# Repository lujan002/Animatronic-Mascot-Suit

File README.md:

# Junior-Jay Animatronic Mascot 

Watch overview video [here](https://youtu.be/p1z4z74mzpA)

The scope of this project was to develop a wearable, Disney-style, animatronic suit with actuated facial features for the University of Kansas's flagship line of "Jayhawk" mascots. The project was sponsored by the Mechanical Engineering Department at the University of Kansas, with the primary client being the University of Kansas head mascot coach. The initiative aimed to revolutionize the university's mascot program by incorporating advanced, expressive features into a new mascot called "Junior Jay". The primary requirements outlined by the client included the ability for the mascots to display a wide range of dynamic, real-time facial expressions, like those seen in professionally animated characters. 

Designing an entirely new mascot head from the ground up was not feasible for the financial and time contraints of this project, so the University of Kansas athletics department graciously donated a retired "Baby Jay" mascot head for the team to retrofit into a proof-of-concept prototype for Junior Jay. Without their support, this project would not be possible. 

This project provided a great mix of mechanical, electrical, and software engineering challanges. The engineering objectives were to modify this retired mascot head with seamless control of the mouth, eyebrow, and eyelid actuation mechanisms using custom facial expression detection & control software, while maintaining durability, comfort, and ease of use. The project started in Aug. 2023 with initial drafts of mechanical models, code, and electrical schematics, then concluded in late Apr. 2024 with a functional protoype that met the majority of our project objectives. Below will be an outline of the final state of these three systems. 

## Mechanism Sub-Systems
### Beak  

Goal: Open/close beak to simulate smile, shock.

The beak assembly consisted of a lightweight aluminum frame inserted into the original, detached foam beak to provide rigidity and a means for the servo motors to drive the beak. We selected servos rated for 45 kg·cm of torque, suitable for the high-torque demands of our application. This choice was driven by the requirement to counter the beak weight of 0.7 kg (6.87 N), with center of gravity centered 230 mm away (1.58 Nm Torque). After installation, the foam beak was re-stitched to the rest of the head for aesthetic purposes. A primary focus was on ensuring robustness and minimizing weight, and the final frame design shown below was no more than 0.4 kg. 

### Eyebrows  

Goal: Rotate eyebrows to display nuanced emotions. 

To enable the mascot to express nuanced emotions, precise control over the eyebrows was essential. The final design acheived this by incorporating each eyebrow as one of the links in a three-bar linkage driven by two servos. This gave each eyebrow two ways to pivot, and thus 2 DOF. Each servo connects to one of the other two links, one which keeps its pivot at a fixed distance, and one wich has a slider cutout that allowed for its pivot to translate back and forth. The result is that the eyebrow can raise and lower itself without changing the angle it is oriented at (thus height and angle can be controlled separetely). Given the aesthetic design constraints, the eyebrow actuation mechanisms were concealed inside the head and behind the eyebrow. This in turn necessitated custom-printed shaft extentions so the servo shafts could reach through small holes in the forehead to connect to the links on the outside of the head. Press-fit threaded inserts and a star pattern connection on the shafts ensured the arms did not slip.

### Eyelids  

Goal: Open/close eyelids to simulate blinking.

To enable the animatronics' eyelid functionality, the eyes of the original mascot head had to be removed and offset a small distance to give space for the eyelid fabric to operate. The opportunity to fully rework the eye design was taken. This process involved vacuum forming a PETG plastic sheet over a 3D printed buck, which was then painted with a one-way reflective mirror coating. This new eye was mounted to a frame, along with, conveniently, all the eyelid actuation mechanicms and even the eyebrow servos. This allowed for easy removal of the whole assembly when maintentnce was required. The frame was designed to support the eyebrow mechanics while providing enough space for the eyelid material to spool without increasing in diameter. For eyelid actuation, a compact timing belt system was chosen instead of gears or chains due to its reliability and quiet operation (similar to those used in 3D printers). The eyelid fabric was stiched directly to the belt. 

Initially, a DC motor was considered for this system, but its torque, size, and control limitations led to the selection of a continuous servo motor, which offers sufficient torque and simpler control. To compensate for the servo's slower speed, a gear system was incorporated to increase the speed of the eyelid movement while maintaining the necessary torque for smooth operation. Unlike a normal servo, the continuous servo has no positional feedback. To work around this, two limit switches were added to shut off the motors when tripped. A small object stiched to the belt would trip one switch when the eye was fully open, and the other when fully closed, thus shutting off the motors. 

To better understand how this system works, please watch the docummentation video linked earlier. 

## Expression Detection & Control Software 

Arguably the part of this project with the most innovative potential, and deviation from traditional animatronic models, is the integration of facial detection technology to control the mechanical systems described above. The software algorithm is actually a single “master” python script (master_script.py) running on the Raspberry Pi, which 
handles everything from the capturing of video frames, detection of faces, prediction of a facial expression, and sending of signal to the motors to adjust servo angles to mimic the detected expression.

Early in the development process, it was decided that due to computational limitations of the Raspberry Pi and to avoid jittery mechanical movements, the software would predict discrete emotions and control the motors in set configurations. The emotions to be predicted were "neutral", "angry", "happy", "surprised", and "sad". Separetely, the mouth and eyes would be predicted as "open" or "closed". This approach was chosen over a design that would mimic every nuanced movement of the wearer, prioritizing smooth and stable operation of the mascot.

The facial detection was naturally split up into different sections based on the mechanical sub-system that it would control. For control of the eyes and mouth, first open-source computer vision libraries were used to extract the coordinates of the facial landmarks (eyes and mouth in this case). Expressions were then classified by measuring the distance between a select few coordinates, such as the outer-most and upper/lower-most mouth edges, and calculating an aspect ratio (mouth height/mouth width). Naturally, when the eyes or mouth are closed, this aspect ratio decreases. Thus, a certain empirically determined ratio was selected and compared with each incoming frames to label the mouth/eyes as "closed" if below the threshold, and "open" if above the threshold. The method implemented in the final master script uses the dlib facial landmark model, although Google's MediaPipe model was also considered.

<!-- Insert EAR,MAR picture here  -->

The movement of the eyebrows, arguably the most important mechanical sub-system in dynamic emotion display, was more intricate. Two approaches were tested for detecting the wearer's emotion out of the five discrete emotions. The first approach used a similar approach to the mouth and eye detection, this time using the eyebrow facial landmark coordinates to come up with some ratio. This posed a more tricky problem that with the eyes and mouth however, as it was quickly realised that predicting emotions based on the eyebrows alone for emotions like sad, happy, and neutral were quite subtle. It would have been possible to combine the eyebrow ratio with a ratio for other landmarks on the face, but ultimately it was decided that a more effective approach would be to use an image classification model to predict discrete emotions. 

A convolutional neural network (CNN) was trained on the [FER-2013 dataset](https://www.kaggle.com/datasets/msambare/fer2013) (Facial Emotion Recognition) to classify facial expressions. The training process is documented in train-emotion-detection.py. The original pre-trained model is attached directly as model_optimal2.h5. This model was converted to a tensorflow.lite model (saved as model.tflite in convert_to_tflite.py), which is directly used in master_script.py. Readers interested in the implementation of this model, its archeture, or the training process are encouraged to reveiw these scripts. The model achieves over 75% accuracy on the validation dataset, with even better performance observed in practical use (potentially a result of the FER-2013 dataset's well-known problem with inconsistent labeling). 

In order to ensure the program could run as close to real-time as possible, steps were taken to reduce the computational load. One simple approach used was to limit the number of frames processed. Several different frame rates were tested, and ultimately 5 fps was chosen as a nice balance between computational low cost and quick enough updates. The images were also converted to greyscale before processing, which is what the model was trained on and also happens to be more computationally efficient. The model was run using Google’s TensorFlow.Lite library, which is purpose built for running models on lighter hardware. Challenges in detecting faces within the dark, close-up environment inside the mascot's head, even with the use of a low-light, wide-angle camera, hindered the successful demonstration of the internal camera functionality. Efforts to improve face detection under these conditions included enhancing illumination and artificially padding the frame borders to create the illusion of a more distant face. For our demonstration purposes, the camera was positioned outside the head. Future work is required to fully achieve the project's initial objectives under these specific conditions. 

Whatever the approach, signals to the servos were sent from the designated GPIO pins using the pigpio library. 
<!-- Readers can test the standalone software functionality by installing the packages in requirements.txt and runnign software_demo.py -->

## Electrical System

The electrical system composed of 50,000 mAh battery pack specifically chosen for a 2hr. lifetime (or that of a typical basketball game), its three USB type A and C ports, and its 5-20V capacity. This battery choice was driven by the aforementioned 45 kg·cm servos we selected required 9V power to achieve our torque target. Two HUSB238 power delivery breakouts configured to draw 5V and 9V respectively were connected the USB ports on the battery. The Raspberry Pi was directly connected to the third port. In this configuration, all the servos requiring 5V (eyelid and eyebrow servos) were powered separately from the 9V servos (beak servos). Miscellaneous components such as the eyelid limit switches, fans, camera, and LED indicator panel were to be powered by the Raspberry Pi.  

There were two key considerations when designing this system. This system contains approximately fifty loose wires, and it quickly became apparent that wire management was crucial for easy maintenance, visibility inside the head, and ensuring the integrity of the sensitive wiring. All wires were strategically routed around the internal structure of the head. Wires were systematically braided and grouped by sub-system, labeled, and secured to prevent obstruction of vision, reduce tangling risks, and simplify maintenance procedures. A Raspberry Pi GPIO pin extension board with screw clamps was used and gave much needed easy accessibility when pulling and plugging wires. A power bus was designed and implemented that handled the distribution of power to all motors in a convenient location. Since these electrical components would be operating very close to a human’s face, safety was also a top priority. Initial testing done on the 9V beak servos under high load produced worrying results on the multimeter. In some cases, the current draw of an individual servo could spike to well over 1A. To prepare for dangerous current spikes like this, two 1Ω power resistors in series were added to the 9V rail on the power bus to dissipate any excess current as heat. An emergency safety switch was also added to shut the 9V motors off.  

### Voltage Converter PCB
The servos that move the lower beak were chosen for their high torque at operating volages above 5V. The servos used were actually rated for 5V - 8.4V, so initially a voltage converter circuit was designed to step down the input voltage to 8V. Later it was realized that the servos could run on 9V directly from the power bank, making this voltage converter irrelevant. Regardless, an short summary of the work done on it will be listed. A [dummy breakout](https://www.adafruit.com/product/5807) was used to draw 12V from the [power bank](https://www.amazon.com/Charging-50000mAh-Portable-Compatible-External/dp/B0C5D1JR2K/ref=asc_df_B0C5D1JR2K/?tag=hyprod-20&linkCode=df0&hvadid=663345862487&hvpos=&hvnetw=g&hvrand=11970480634190944901&hvpone=&hvptwo=&hvqmt=&hvdev=c&hvdvcmdl=&hvlocint=&hvlocphy=1017537&hvtargid=pla-2188333650925&psc=1&mcid=6e21d341f4533a22af8d0ba4956a6da5), which was further stepped down to 8V by this circuit. 

The schemetic shown below incorporates an [LM317 Voltage Regulator](https://www.ti.com/product/LM317-N/part-details/LM317T/NOPB?HQS=ocb-tistore-invf-buynowlink_partpage-invf-store-snapeda-wwe) ([footprint](https://www.snapeda.com/parts/LM317T/NOPB/Texas%20Instruments/view-part/)) and a series of commonly available resistors.

The board was designed in KiCAD and printed at the school shop.

### Emotion LED Indicator Panel
One concern during operation of the animatronic was that the wearer would have no idea what expression was currently being used. The beak and eyelids would be obvious enough to the wearer if they were open or closed, but there would be no way of knowing the current state of the eyebrows. An LED panel indicator panel was designed as a solution to this. The panel was planned to be mounted inside the head and include seven LEDs, five for each of the discrete emotions, one LED for the mouth state, and one for the eye state. This would tell the wearer inside if the expression detection program is working as intended. Ultimately time constraints prevented the implementation of this optional feature, but the concept was proven to work. 

The board was designed in KiCAD and printed at the school shop.

### Future Work

While the project has made significant strides in demonstrating that the functionality and appeal of university mascots can be dramatically improved, there remains scope for further development to fully realize the envisioned goals. Future work could focus on several areas to refine and expand the project's achievements: 

1.  Refinement of Mechanical Systems: Further refinement of the mechanical systems controlling facial expressions is essential. Continuous testing and iteration could lead to more fluid and natural movements, reducing any mechanical lag or stiffness currently present. 
2.  Advanced AI and Machine Learning: Implementing more sophisticated AI algorithms and machine learning techniques, such as training on a larger dataset or a custom dataset built to our specific needs, could enhance the accuracy and responsiveness of the facial recognition system. Also, work can be done to give more nuanced expressions prediction rather than the simpler discrete expression approach used. This would ensure a more precise and seamless translation of the performer’s expressions to the mascot. 
3.  Enhanced Cooling Technologies: Although the current cooling system provides basic relief, exploring advanced technologies like phase change materials or more efficient heat exchange mechanisms could offer better temperature regulation, increasing comfort during longer performances or in more extreme weather. 
4.  Integration of Interactive Technologies: Adding interactive technologies such as voice modulation and responsive sound systems could make the mascots even more engaging. For instance, allowing the mascots to respond vocally to crowd interactions or integrate sound effects linked to their movements could greatly enhance audience interaction. 
5.  Sustainability and Materials Science: Investigating more sustainable materials and construction techniques that maintain durability while reducing weight could improve the ergonomics and environmental impact of the mascot costumes. 
6.  Extended Wearability Studies: Conducting extended wearability studies to gather data on the performer's comfort and suit ergonomics over longer periods can provide insights into necessary adjustments and improvements. 
7.  Scalability and Transferability: Finally, considering how these enhancements can be standardized and transferred to other mascot programs could broaden the impact of the project. Developing a modular system that can be customized and adapted to different mascots could make these advancements more accessible to other institutions. 
8.  Foolproof electrical safety measures: A mechanical cover should be added to cover the power bus to protect against accidental contact and reduce the risk of short circuits. Additionally, wiring may be optimally routed inside the head wall to minimize exposure and vulnerability. Safety devices such as fuses, and micro-circuit breakers will be incorporated to prevent electrical overloads and potential hazards.  

These areas of future work would not only address the remaining challenges, but also push the boundaries of what is possible in mascot design and performance - potentially setting new industry standards. 

For a full detail of the technical work involved in the project, please refer to the "Junior Jay Final Poster" and "Junior Jay Final Report" documents.

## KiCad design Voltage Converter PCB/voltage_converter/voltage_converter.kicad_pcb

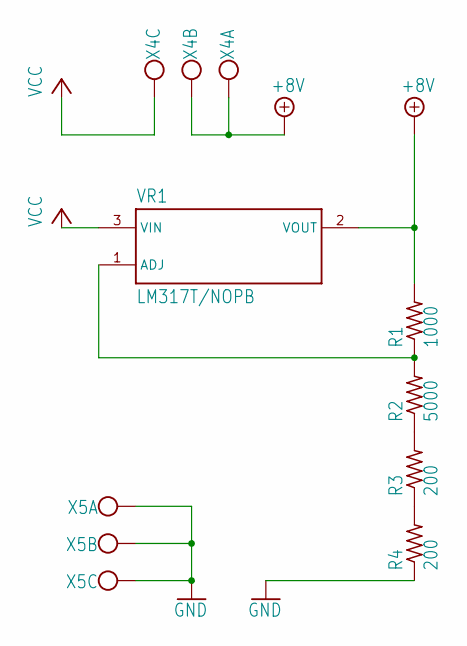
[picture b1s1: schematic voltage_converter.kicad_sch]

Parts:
R1: 1000; 0204_5
R2: 5000; 0204_5
R3, R4: 200; 0204_5
VR1: LM317T/NOPB; TO254P1054X470X1955-3
X4, X5: W237-103

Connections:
+8V: R1.2, VR1.2 (VOUT), X4.1, X4.2
GND: R4.1, X5.1, X5.2, X5.3
unnamed: R3.1, R4.2
unnamed: R2.1, R3.2
unnamed: R1.1, R2.2, VR1.1 (ADJ)
VCC: VR1.3 (VIN), X4.3

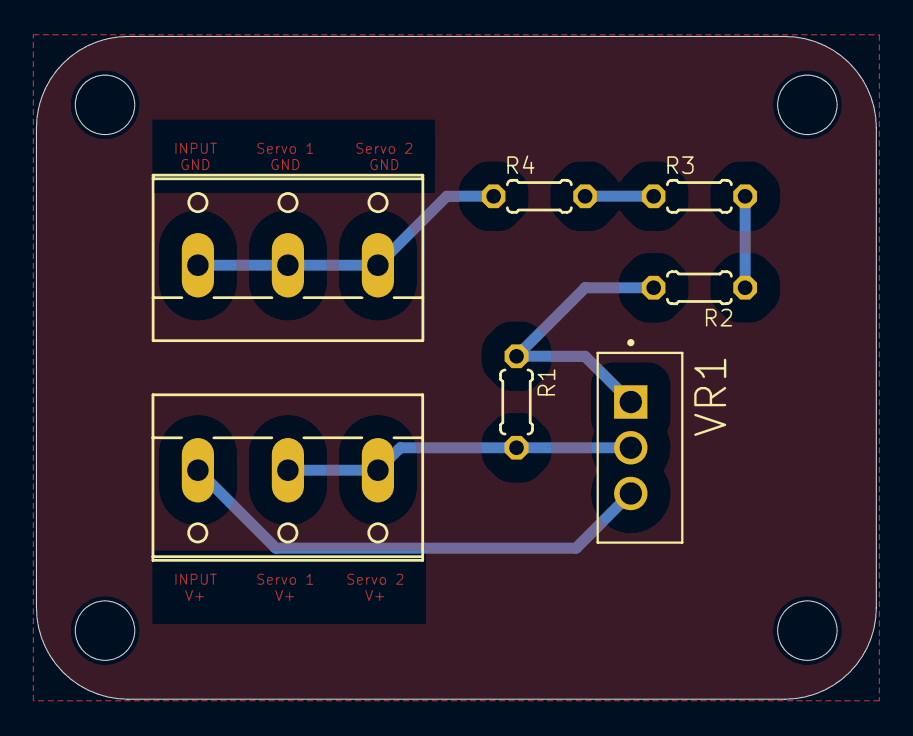
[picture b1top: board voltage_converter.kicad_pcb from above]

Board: 2 copper layers, 46.7 x 36.8 mm, 11 parts (0 on the bottom side), 6 nets.

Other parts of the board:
@HOLE0, @HOLE1, @HOLE2, @HOLE3: (no value)

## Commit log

2024-03-06 changed README
2024-03-06 added video
2024-03-27 added cv code
2024-03-27 first commit from raspberry pi
2024-03-29 updated for pi test
2024-04-07 updating after succesful emotion detection test
2024-04-07 updated read me
2024-04-09 adding vc pcb, model 3, test code for eye/mouth detection
2024-04-09 updated readme with pcb documentation
2024-04-09 moved pcb png's to the root folder
2024-04-09 wrapped links
2024-04-12 consolidated facial detection, added battery_basket, new voltage converter board
2024-04-12 added independent EAR tracking option
2024-04-13 adding two servo slider script
2024-04-13 added led outputs for emotion detection
2024-04-13 adding tflite compatibility
2024-04-13 adding quantization to tflite converter
2024-04-13 updating model.tflite
2024-04-13 facial emotion detection working pretty well
2024-04-19 refined v7 w/sad bias, added RPi GPIO tests
2024-04-20 changing combined script v8 to add arduino serial integration
2024-04-20 added new PCBs, eyelid test, arduino case
2024-04-21 splitting v8 into arduino and RPi versions, renaming RPi scripts
2024-04-21 updating README with newer images
2024-04-21 fixed failed update of beak images
2024-04-21 updated README with new beak png name
2024-04-21 adding facial detection tests
2024-04-21 adding 3D parts
2024-04-22 adding v9 with new facial detection (ResNet), and saved relevent model files (prototxt, res10)
2024-04-22 adding servo shaft 3D files
2024-04-22 using mediapipe as the face detector for v9
2024-04-22 adding new battery basket
2024-04-22 creating v10, which uses mediapipe instead of dlib for eye, mouth detection
2024-04-22 adding camera 3D mounts
2024-04-23 adding emotion pictures, using mediapipe for v9
2024-04-24 reorgainizing 3D Parts Files
2024-04-26 adding Scott's pictures, poster, electrical diagram
2024-04-26 eybrows and beak working smoothly
2024-04-26 updating packages install guide
2024-04-29 adding new pictures, updating readme
2024-04-29 fixing images in readme
2024-04-29 removing unecessary files
2024-05-03 renaming main script
2024-05-05 adding final report
2024-05-05 testing removal of model_optimal.h5
2024-05-05 test removal cached files
2024-05-05 adding back files???
2024-05-05 reverting to commit 6a28e0f5d63627f6d088ff7bae5bab4ce5145466
2024-05-05 rm all and pushing with only essential files
2024-05-05 Committing changes to Junior Jay Python Packages Install Guide.odt
2024-05-05 updating git ignore
2024-05-05 trying rm cached again
2024-05-05 work in progress README
2024-05-06 adding better pictures, description to README
2024-05-06 fixing minor typos
2024-05-16 Added new overview video to read me
